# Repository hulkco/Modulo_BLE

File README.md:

Modulo_BLE
Footprint para modulo MS88SF2/nRF52840 de Minew

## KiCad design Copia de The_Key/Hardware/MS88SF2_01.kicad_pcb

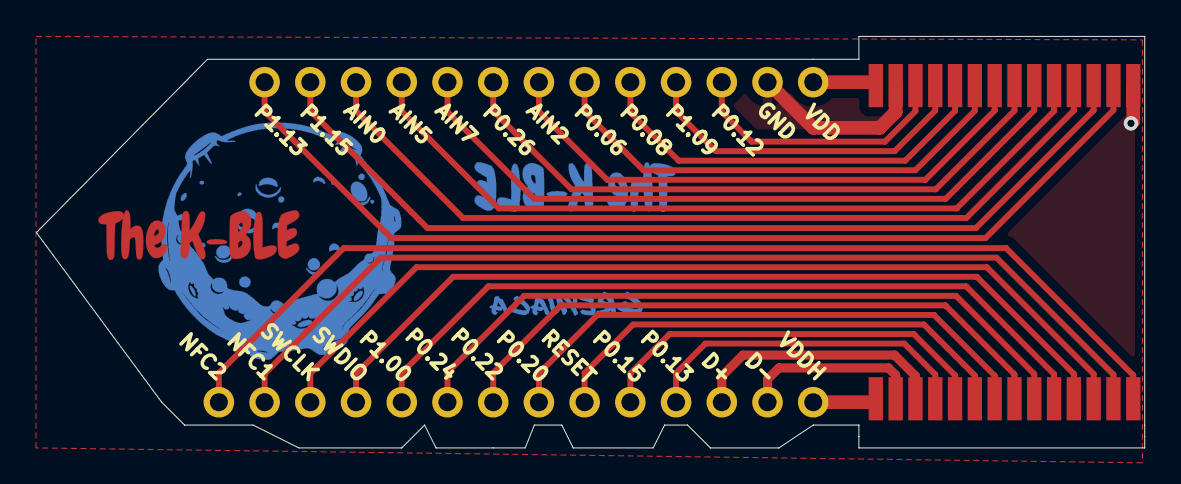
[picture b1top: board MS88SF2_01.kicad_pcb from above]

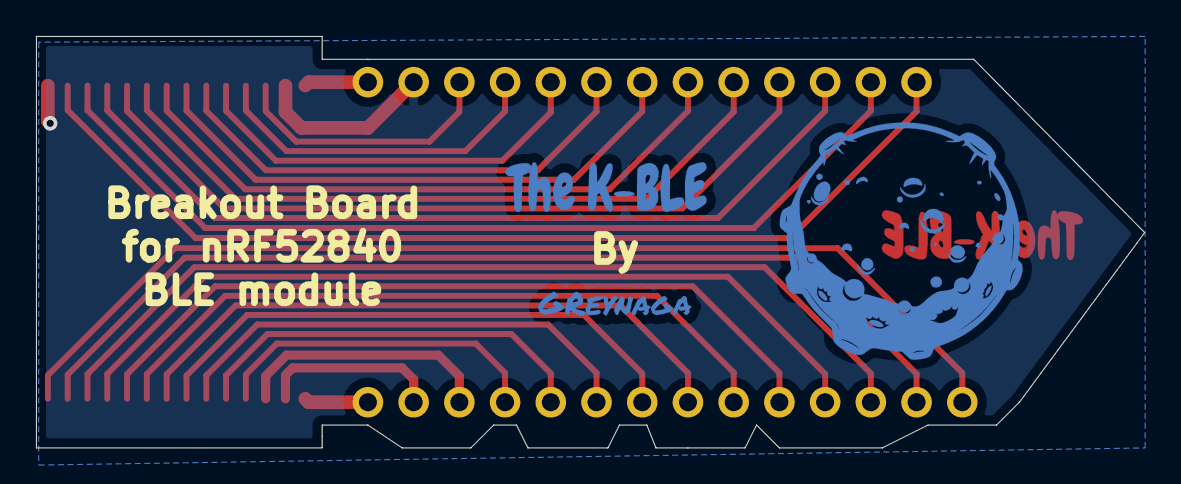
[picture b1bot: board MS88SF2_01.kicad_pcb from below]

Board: 2 copper layers, 61.6 x 22.9 mm, 7 parts (3 on the bottom side), 27 nets.

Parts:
J1: Conn_01x13_Female; PinSocket_1x13
J2: Conn_01x14_Female; PinSocket_1x14
Ref**: Val**; Letters
Ref**#2: Val**; Moon
Ref**#3: Val**; Letters
U1: MS88SF2
U2: Firma; firma_Cu_Mask

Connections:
/D+: J2.12, U1.17
/D-: J2.13, U1.16
/P0.02-AIN0: J1.3, U1.4
/P0.04-AIN2: J1.7, U1.8
/P0.06: J1.8, U1.9
/P0.08: J1.9, U1.10
/P0.09-NFC1: J2.2, U1.27
/P0.10-NFC2: J2.1, U1.28
/P0.12: J1.11, U1.12
/P0.13: J2.11, U1.18
/P0.15: J2.10, U1.19
/P0.18-RESET: J2.9, U1.20
/P0.20: J2.8, U1.21
/P0.22: J2.7, U1.22
/P0.24: J2.6, U1.23
/P0.26: J1.6, U1.7
/P0.29-AIN5: J1.4, U1.5
/P0.31-AIN7: J1.5, U1.6
/P1.00: J2.5, U1.24
/P1.09: J1.10, U1.11
/P1.13: J1.1, U1.2
/P1.15: J1.2, U1.3
/SWCLK: J2.3, U1.26
/SWDIO: J2.4, U1.25
/VDDH: J2.14, U1.15
GND: J1.12, U1.1, U1.13
VDD: J1.13, U1.14

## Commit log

2021-11-03 Add files
